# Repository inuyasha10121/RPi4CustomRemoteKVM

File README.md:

# RPi4CustomRemoteKVM
A custom remote KVM setup based around a Raspberry Pi 4.

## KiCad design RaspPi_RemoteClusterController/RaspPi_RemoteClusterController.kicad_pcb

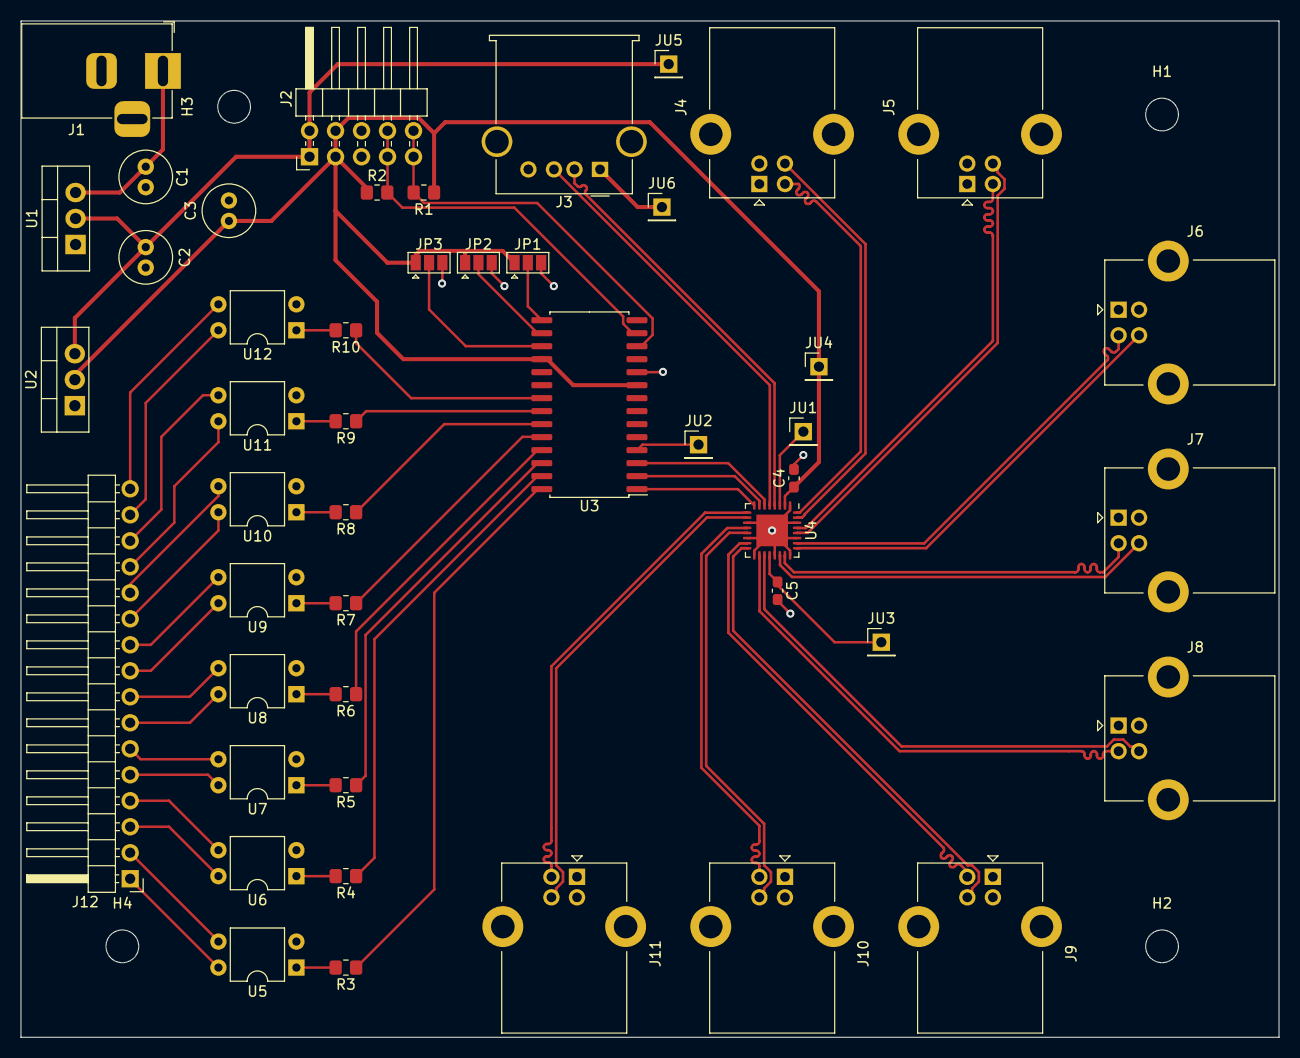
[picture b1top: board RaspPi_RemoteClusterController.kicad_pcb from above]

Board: 2 copper layers, 122.9 x 99.3 mm, 52 parts (0 on the bottom side), 66 nets.

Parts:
C1, C2, C3: 10uF; C_Radial_D5.0mm_H11.0mm_P2.00mm
C4, C5: 0.1uF; C_0603_1608Metric_Pad1.08x0.95mm_HandSolder
H1, H2, H3, H4: MountingHole; MountingHole_3.2mm_M3
J1: Jack-DC; BarrelJack_Horizontal
J2: Conn_01x10; PinHeader_2x05_P2.54mm_Horizontal
J3: USB_A; USB_A_Molex_67643_Horizontal
J4, J5, J6, J7, J8, J9, J10, J11: USB_B; USB_B_Lumberg_2411_02_Horizontal
J12: Conn_01x16; PinHeader_1x16_P2.54mm_Horizontal
JP1, JP2, JP3: Addr; SolderJumper-3_P1.3mm_Open_Pad1.0x1.5mm
JU1, JU2: GPB3_Jump; PinHeader_1x01_P2.54mm_Vertical
JU3, JU4: 3.3V_Jump; PinHeader_1x01_P2.54mm_Vertical
JU5, JU6: 5V_Jump; PinHeader_1x01_P2.54mm_Vertical
R1, R2: 1k; R_0805_2012Metric_Pad1.20x1.40mm_HandSolder
R3, R4, R5, R6, R7, R8, R9, R10: 100; R_0805_2012Metric_Pad1.20x1.40mm_HandSolder
U1: LT1085-5.0; TO-220-3_Vertical
U2: LT1085-3.3; TO-220-3_Vertical
U3: MCP23017_SO; SOIC-28W_7.5x17.9mm_P1.27mm
U4: MAX4999
U5, U6, U7, U8, U9, U10, U11, U12: PC817; DIP-4_W7.62mm

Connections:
+3V3: C3.1, C4.1, J2.3, J2.4, JP1.1 (A), JP2.1 (A), JP3.1 (A), JU4.1, R1.1, R2.1, U2.2 (VO), U3.9 (VDD), U3.18 (~RESET), U4.2 (+3V3)
+5V: C2.1, J2.1, J2.2, JU5.1, U1.2 (VO), U2.3 (VI)
+6V: C1.1, J1.1, U1.3 (VI)
/COM+: J3.3 (D+), U4.5 (COM+)
/COM-: J3.2 (D-), U4.4 (COM0-)
/D0+: J11.3 (D+), U4.10 (D0+)
/D0-: J11.2 (D-), U4.9 (D0-)
/D1+: J10.3 (D+), U4.13 (D1+)
/D1-: J10.2 (D-), U4.12 (D1-)
/D2+: J9.3 (D+), U4.16 (D2+)
/D2-: J9.2 (D-), U4.15 (D2-)
/D3+: J8.3 (D+), U4.19 (D3+)
/D3-: J8.2 (D-), U4.18 (D3-)
/D4+: J7.3 (D+), U4.22 (D4+)
/D4-: J7.2 (D-), U4.23 (D4-)
/D5+: J6.3 (D+), U4.25 (D5+)
/D5-: J6.2 (D-), U4.26 (D5-)
/D6+: J5.3 (D+), U4.28 (D6+)
/D6-: J5.2 (D-), U4.29 (D6-)
/D7+: J4.3 (D+), U4.31 (D7+)
/D7-: J4.2 (D-), U4.32 (D7-)
GND: C1.2, C2.2, C3.2, C4.2, C5.2, J1.2, J2.5, J2.6, J3.4 (GND), J3.5 (Shield), J4.4 (GND), J4.5 (Shield), J5.4 (GND), J5.5 (Shield), J6.4 (GND), J6.5 (Shield), J7.4 (GND), J7.5 (Shield), J8.4 (GND), J8.5 (Shield), J9.4 (GND), J9.5 (Shield), J10.4 (GND), J10.5 (Shield), J11.4 (GND), J11.5 (Shield), JP1.3 (B), JP2.3 (B), JP3.3 (B), U1.1 (GND), U2.1 (GND), U3.10 (VSS), U4.1 (GND), U4.11 (GND), U4.14 (GND), U4.17 (GND), U4.21 (GND), U4.24 (GND), U4.27 (GND), U4.30 (GND), U4.33 (EP), U5.2, U6.2, U7.2, U8.2, U9.2, U10.2, U11.2, U12.2
unnamed: C5.1, JU3.1, U4.20 (+3V3)
unnamed: J2.7, J2.8, R2.2, U3.13 (SDA)
unnamed: J2.9, J2.10, R1.2, U3.12 (SCK)
unnamed: J3.1 (VBUS), JU6.1
unnamed: J12.1, U5.4
unnamed: J12.2, U5.3
unnamed: J12.3, U6.4
unnamed: J12.4, U6.3
unnamed: J12.5, U7.4
unnamed: J12.6, U7.3
unnamed: J12.7, U8.4
unnamed: J12.8, U8.3
unnamed: J12.9, U9.4
unnamed: J12.10, U9.3
unnamed: J12.11, U10.4
unnamed: J12.12, U10.3
unnamed: J12.13, U11.4
unnamed: J12.14, U11.3
unnamed: J12.15, U12.4
unnamed: J12.16, U12.3
unnamed: JP1.2 (C), U3.15 (A0)
unnamed: JP2.2 (C), U3.16 (A1)
unnamed: JP3.2 (C), U3.17 (A2)
unnamed: JU1.1, U4.3 (EN)
unnamed: JU2.1, U3.4 (GPB3)
unnamed: R3.1, U3.28 (GPA7)
unnamed: R3.2, U5.1
unnamed: R4.1, U3.27 (GPA6)
unnamed: R4.2, U6.1
unnamed: R5.1, U3.26 (GPA5)
unnamed: R5.2, U7.1
unnamed: R6.1, U3.25 (GPA4)
unnamed: R6.2, U8.1
unnamed: R7.1, U3.24 (GPA3)
unnamed: R7.2, U9.1
unnamed: R8.1, U3.23 (GPA2)
unnamed: R8.2, U10.1
unnamed: R9.1, U3.22 (GPA1)
unnamed: R9.2, U11.1
unnamed: R10.1, U3.21 (GPA0)
unnamed: R10.2, U12.1
unnamed: U3.1 (GPB0), U4.8 (C2)
unnamed: U3.2 (GPB1), U4.7 (C1)
unnamed: U3.3 (GPB2), U4.6 (C0)

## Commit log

2023-05-01 Uploaded KiCAD project for custom control board
    Uploaded design files for custom 1-to-8 USB Switch and optocoupler-based power control board
